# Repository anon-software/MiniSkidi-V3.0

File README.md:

* Video at [youtube.com/watch?v=dDfVdGGrf1k](https://www.youtube.com/watch?v=dDfVdGGrf1k)
* Kits at [professorboots.com/products/rc-skidsteer-kit-v3-0](https://professorboots.com/products/rc-skidsteer-kit-v3-0?utm_medium=product_shelf)
* Tutorial at [professorboots.com/a/members](https://professorboots.com/a/members) (If self sourcing the parts you'll need to pay for a membershp to unlock that specific course)
* [3D Printed RC SkidSteer V3.0 printables](https://www.printables.com/de/model/721244-3d-printed-rc-skidsteer-v30)

The project depends on these libraries (the listed versions were tested):

* Async TCP by ESP32Async 3.4.7
* ESP Async WebServer by ESP32Async 3.8.0
* ESP32Servo by Kevin Harrington, John K. Bennett 3.0.9

Add the following Board Manager URLs:
* https://raw.githubusercontent.com/espressif/arduino-esp32/gh-pages/package_esp32_index.json
* https://raw.githubusercontent.com/ricardoquesada/esp32-arduino-lib-builder/master/bluepad32_files/package_esp32_bluepad32_index.json

The project depends on this boards packages (the listed versions were tested):

* esp32 by Espressif Systems 3.3.0
* esp32_bluepad32 by Ricardo Quesada 4.1.0

# Bluepad32 support for MiniSkidi V3.0

The game controller sketch is based on https://github.com/JohnFodero/MiniSkidi-V3.0. 

## Controls (for PS3)
 * Left X - Bucket Tilt
 * Left Y - Proportional Left Track Forward/Back
 * Right X - Arm Up/Down
 * Right Y - Proportional Right Track Foward Back
 * X - Toggle Lights

 Rumble activates when attempting to drive servos past their limit :)

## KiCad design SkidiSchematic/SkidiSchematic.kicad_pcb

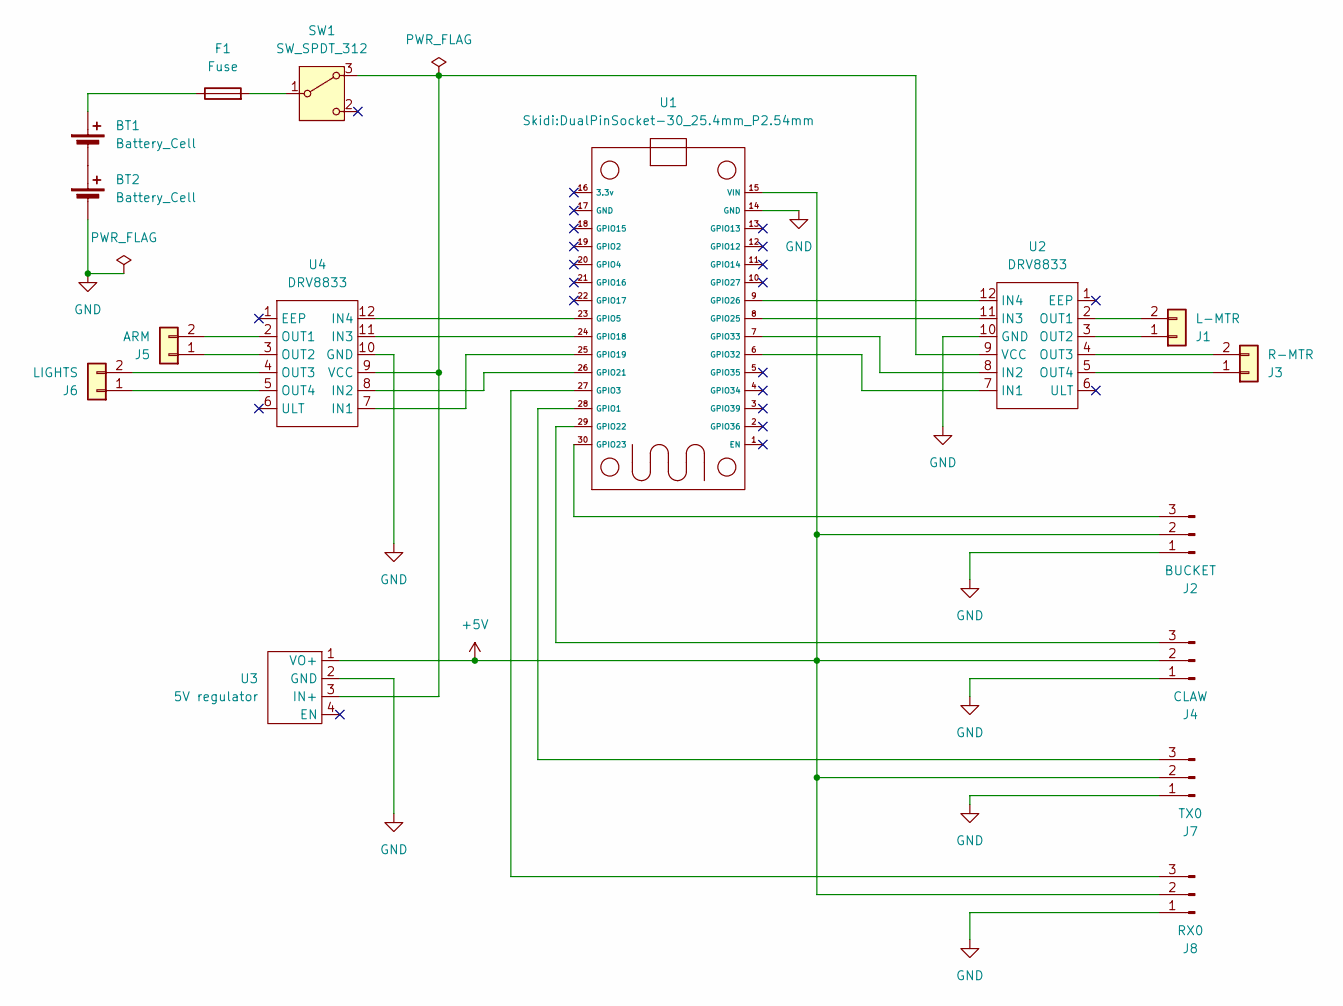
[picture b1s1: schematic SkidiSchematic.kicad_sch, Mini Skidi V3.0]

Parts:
BT1, BT2: Battery_Cell; CR123_holder
F1: Fuse; BLX-A
J1: L-MTR; JST_XH_B2B-XH-A_1x02_P2.50mm_Vertical
J2: BUCKET; PinHeader_1x03_P2.54mm_Vertical
J3: R-MTR; JST_XH_B2B-XH-A_1x02_P2.50mm_Vertical
J4: CLAW; PinHeader_1x03_P2.54mm_Vertical
J5: ARM; JST_XH_B2B-XH-A_1x02_P2.50mm_Vertical
J6: LIGHTS; JST_XH_B2B-XH-A_1x02_P2.50mm_Vertical
J7: TX0; PinHeader_1x03_P2.54mm_Vertical
J8: RX0; PinHeader_1x03_P2.54mm_Vertical
SW1: SW_SPDT_312; SW_Slide-03_SS-12D10_12.7x6.7x6.4_P4.7mm
U1: DualPinSocket-30_25.4mm_P2.54mm
U2, U4: DRV8833; DualPinSocket-12_15.24mm_P2.54mm
U3: 5V regulator; PinHeader_1x04_P2.54mm_Vertical

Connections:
+5V: J2.2, J4.2, J7.2, J8.2, U1.15 (VIN), U3.1 (VO+)
GND: BT2.2 (-), J2.1, J4.1, J7.1, J8.1, U1.14 (GND), U2.10 (GND), U3.2 (GND), U4.10 (GND)
unnamed: BT1.1 (+), F1.1
unnamed: BT1.2 (-), BT2.1 (+)
unnamed: J1.1, U2.3 (OUT2)
unnamed: J1.2, U2.2 (OUT1)
unnamed: J2.3, U1.30 (GPIO23)
unnamed: J3.1, U2.5 (OUT4)
unnamed: J3.2, U2.4 (OUT3)
unnamed: J4.3, U1.29 (GPIO22)
unnamed: J5.1, U4.3 (OUT2)
unnamed: J5.2, U4.2 (OUT1)
unnamed: J6.1, U4.5 (OUT4)
unnamed: J6.2, U4.4 (OUT3)
unnamed: J7.3, U1.28 (GPIO1)
unnamed: J8.3, U1.27 (GPIO3)
unnamed: SW1.3 (A), U2.9 (VCC), U3.3 (IN+), U4.9 (VCC)
unnamed: F1.2, SW1.1 (B)
unnamed: U1.23 (GPIO5), U4.12 (IN4)
unnamed: U1.24 (GPIO18), U4.11 (IN3)
unnamed: U1.25 (GPIO19), U4.7 (IN1)
unnamed: U1.26 (GPIO21), U4.8 (IN2)
unnamed: U1.8 (GPIO25), U2.11 (IN3)
unnamed: U1.9 (GPIO26), U2.12 (IN4)
unnamed: U1.6 (GPIO32), U2.7 (IN1)
unnamed: U1.7 (GPIO33), U2.8 (IN2)

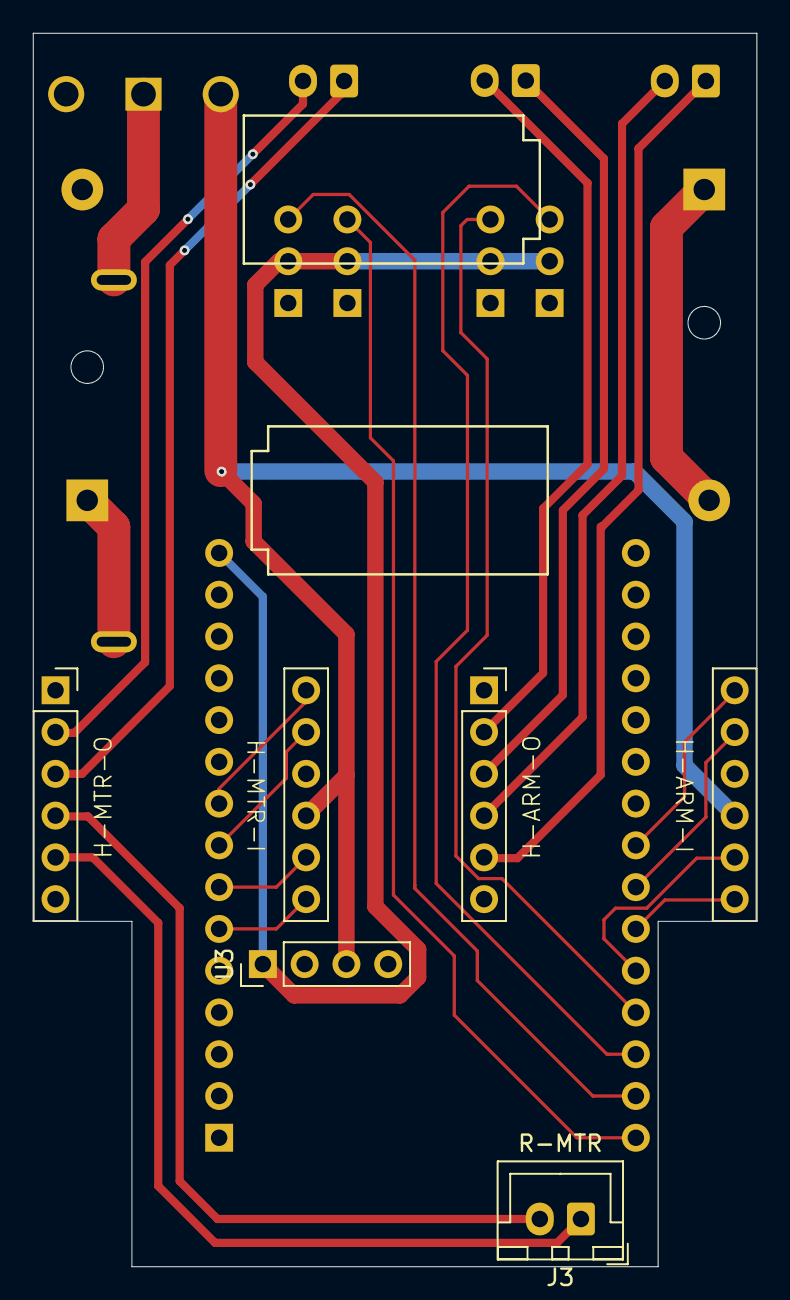
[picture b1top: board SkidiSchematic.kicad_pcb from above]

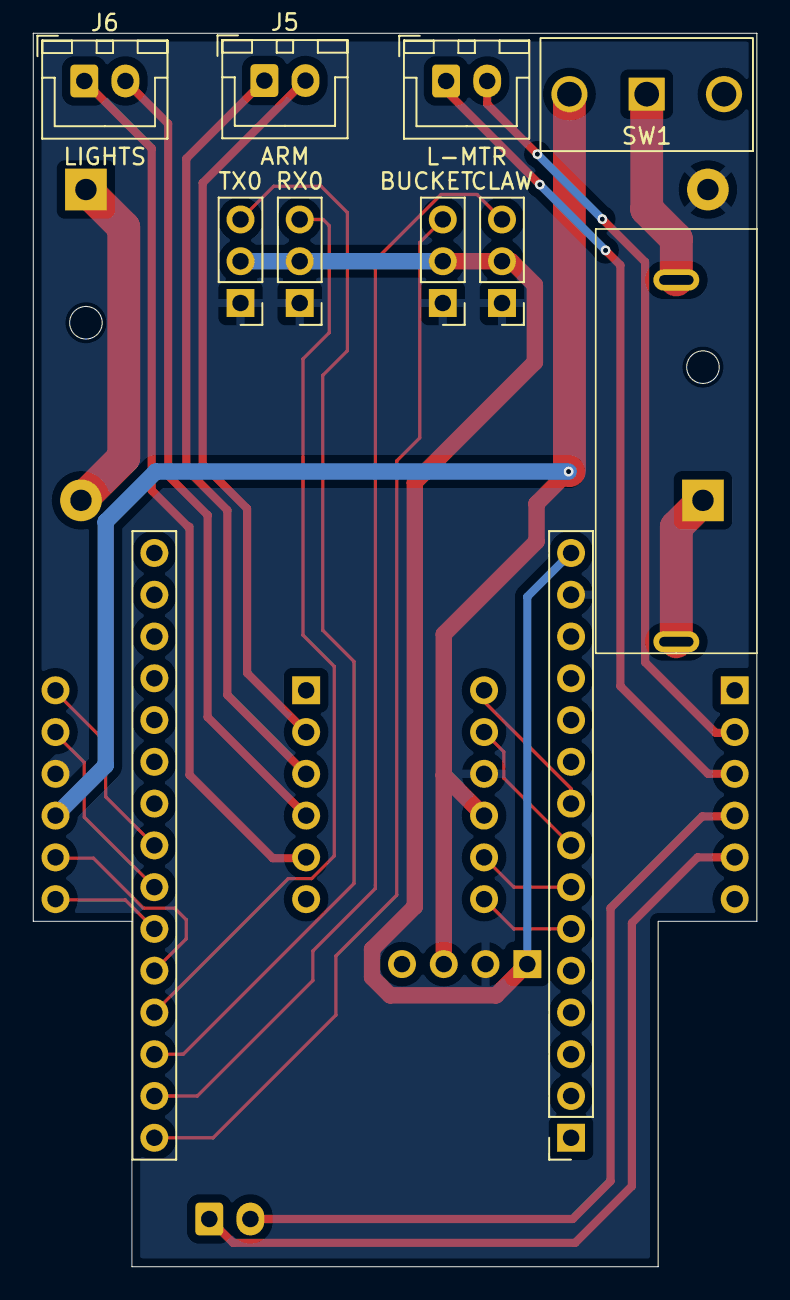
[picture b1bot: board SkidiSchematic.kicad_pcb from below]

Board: 2 copper layers, 44.0 x 75.0 mm, 16 parts (10 on the bottom side), 26 nets.

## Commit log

2025-05-08 Unresolved external linking the web server
    Switching to another library fixes the problem.
2025-06-24 KiCad schematic
    The schematic includes UART connectors for debugging. See
    https://randomnerdtutorials.com/esp32-uart-communication-serial-arduino/
2025-06-24 Adjust the angle ranges for web control
2025-06-26 Add game controller support by John Fodero
    The servo pins are reversed and angle limits adjusted from the original
    implementation.
2025-06-26 Smoother bucket and claw operation
    Dead zone value of 10 seems too low for XBOX controller where an idle
    joystick may outpuvalues as high as 60. We can get away with smaller
    values for the motors.
    The neutral joysticks' position still gives non-zero redouts. The dead
    zone value is there to neutralise them. However, it would be better if
    we can compensate them to some degree. The calibration mode can now be
2025-06-26 Simplified control
    An alternate gamepad control can be toggled by pressing on the B button.
    The left joystick alone controls both motors in this mode which is arguably
    easier.
2025-07-07 Debouncer
2025-08-20 Flip simplified steering when reversing
2025-08-20 Update README with library versions
2025-08-26 Move switch to the other PCB side
2025-08-30 No PWM without logging
    The loop delay that yields the CPU to the PWM maintenance was outside
    the loop and thus not having any effect. Without logging through the
    serial output which itself presumably allows the maintenance thread to
    kick in, the motors practically do not move.
    Interestingly, it somewhat works if channel 8 and above are used. It
    seems that ESP32Servo library designates channels 0-7 as low speed
2025-08-30 Update README file
2025-08-30 Better simplified control
    Based on https://github.com/swholmstead/SkidSteer/blob/main/MiniSkidi_Bluepad_2.0.ino
